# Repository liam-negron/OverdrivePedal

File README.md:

# OverdrivePedal
A custom overdrive guitar pedal with volume, drive, and tone control.\
Video demonstration: https://youtu.be/vQzezkZPXa8

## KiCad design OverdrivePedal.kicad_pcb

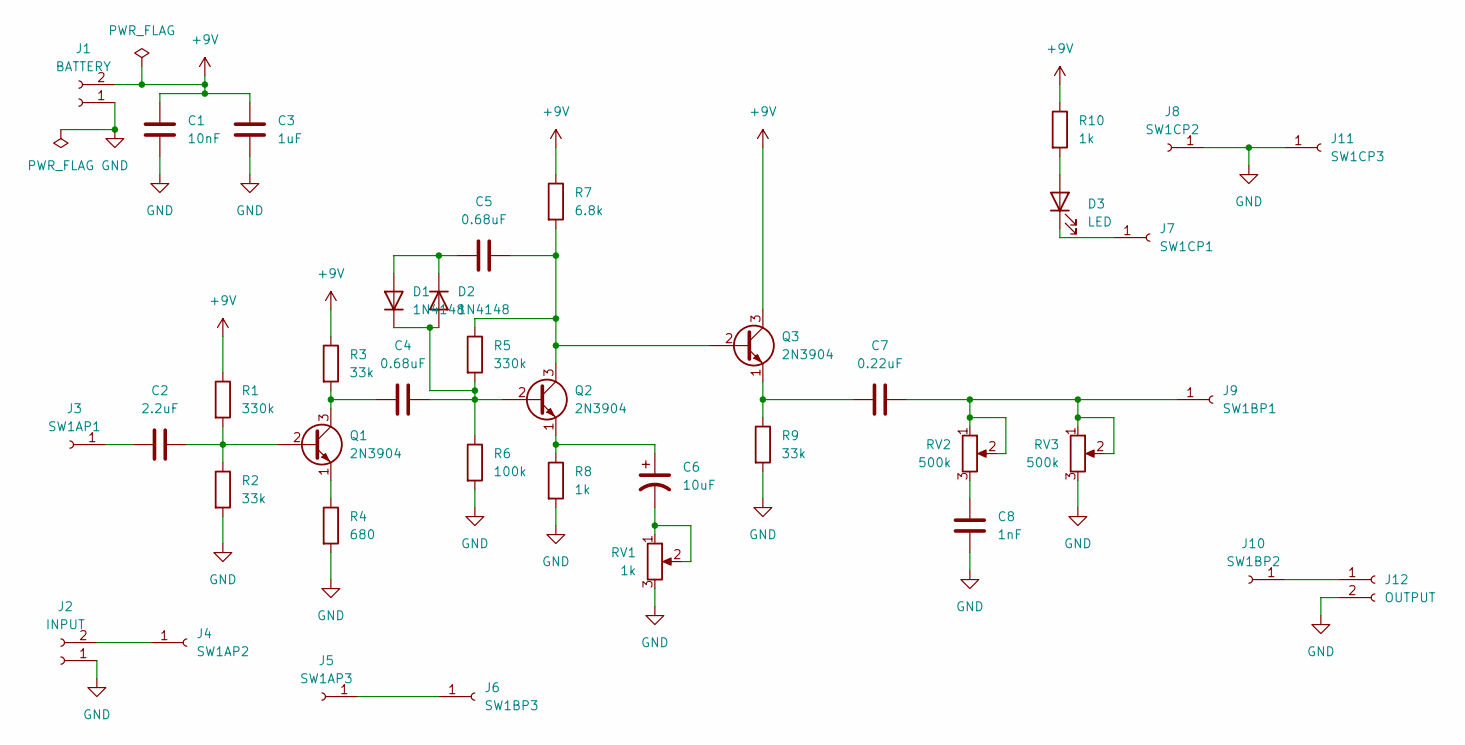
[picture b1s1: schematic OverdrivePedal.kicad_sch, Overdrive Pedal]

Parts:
C1: 10nF; C_Disc_D3.0mm_W1.6mm_P2.50mm
C2: 2.2uF; C_Disc_D3.0mm_W1.6mm_P2.50mm
C3: 1uF; C_Disc_D3.0mm_W1.6mm_P2.50mm
C4, C5: 0.68uF; C_Disc_D3.0mm_W1.6mm_P2.50mm
C6: 10uF; CP_Radial_D4.0mm_P2.00mm
C7: 0.22uF; C_Disc_D3.0mm_W1.6mm_P2.50mm
C8: 1nF; C_Disc_D3.0mm_W1.6mm_P2.50mm
D1, D2: 1N4148; D_DO-35_SOD27_P7.62mm_Horizontal
D3: LED; LED_D3.0mm
J1: BATTERY; PinSocket_1x02_P2.54mm_Vertical
J2: INPUT; PinSocket_1x02_P2.54mm_Vertical
J3: SW1AP1; Pin_D1.0mm_L10.0mm
J4: SW1AP2; Pin_D1.0mm_L10.0mm
J5: SW1AP3; Pin_D1.0mm_L10.0mm
J6: SW1BP3; Pin_D1.0mm_L10.0mm
J7: SW1CP1; Pin_D1.0mm_L10.0mm
J8: SW1CP2; Pin_D1.0mm_L10.0mm
J9: SW1BP1; Pin_D1.0mm_L10.0mm
J10: SW1BP2; Pin_D1.0mm_L10.0mm
J11: SW1CP3; Pin_D1.0mm_L10.0mm
J12: OUTPUT; PinSocket_1x02_P2.54mm_Vertical
Q1, Q2, Q3: 2N3904; TO-92_Inline
R1, R5: 330k; R_Axial_DIN0309_L9.0mm_D3.2mm_P12.70mm_Horizontal
R2, R3, R9: 33k; R_Axial_DIN0309_L9.0mm_D3.2mm_P12.70mm_Horizontal
R4: 680; R_Axial_DIN0309_L9.0mm_D3.2mm_P12.70mm_Horizontal
R6: 100k; R_Axial_DIN0309_L9.0mm_D3.2mm_P12.70mm_Horizontal
R7: 6.8k; R_Axial_DIN0309_L9.0mm_D3.2mm_P12.70mm_Horizontal
R8, R10: 1k; R_Axial_DIN0309_L9.0mm_D3.2mm_P12.70mm_Horizontal
RV1: 1k; Potentiometer_Bourns_3386C_Horizontal
RV2, RV3: 500k; Potentiometer_Bourns_3386C_Horizontal

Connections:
+9V: C1.1, C3.1, J1.2, Q3.3 (C), R1.1, R3.1, R7.1, R10.1
GND: C1.2, C3.2, C8.2, J1.1, J2.1, J8.1, J11.1, J12.2, R2.2, R4.2, R6.2, R8.2, R9.2, RV1.3, RV3.3
unnamed: C2.1, Q1.2 (B), R1.2, R2.1
unnamed: C2.2, J3.1
unnamed: C4.1, D1.1 (K), D2.2 (A), Q2.2 (B), R5.2, R6.1
unnamed: C4.2, Q1.3 (C), R3.2
unnamed: C5.1, Q2.3 (C), Q3.2 (B), R5.1, R7.2
unnamed: C5.2, D1.2 (A), D2.1 (K)
unnamed: C6.1, Q2.1 (E), R8.1
unnamed: C6.2, RV1.1, RV1.2
unnamed: C7.1, J9.1, RV2.1, RV2.2, RV3.1, RV3.2
unnamed: C7.2, Q3.1 (E), R9.1
unnamed: C8.1, RV2.3
unnamed: D3.1 (K), J7.1
unnamed: D3.2 (A), R10.2
unnamed: J2.2, J4.1
unnamed: J5.1, J6.1
unnamed: J10.1, J12.1
unnamed: Q1.1 (E), R4.1

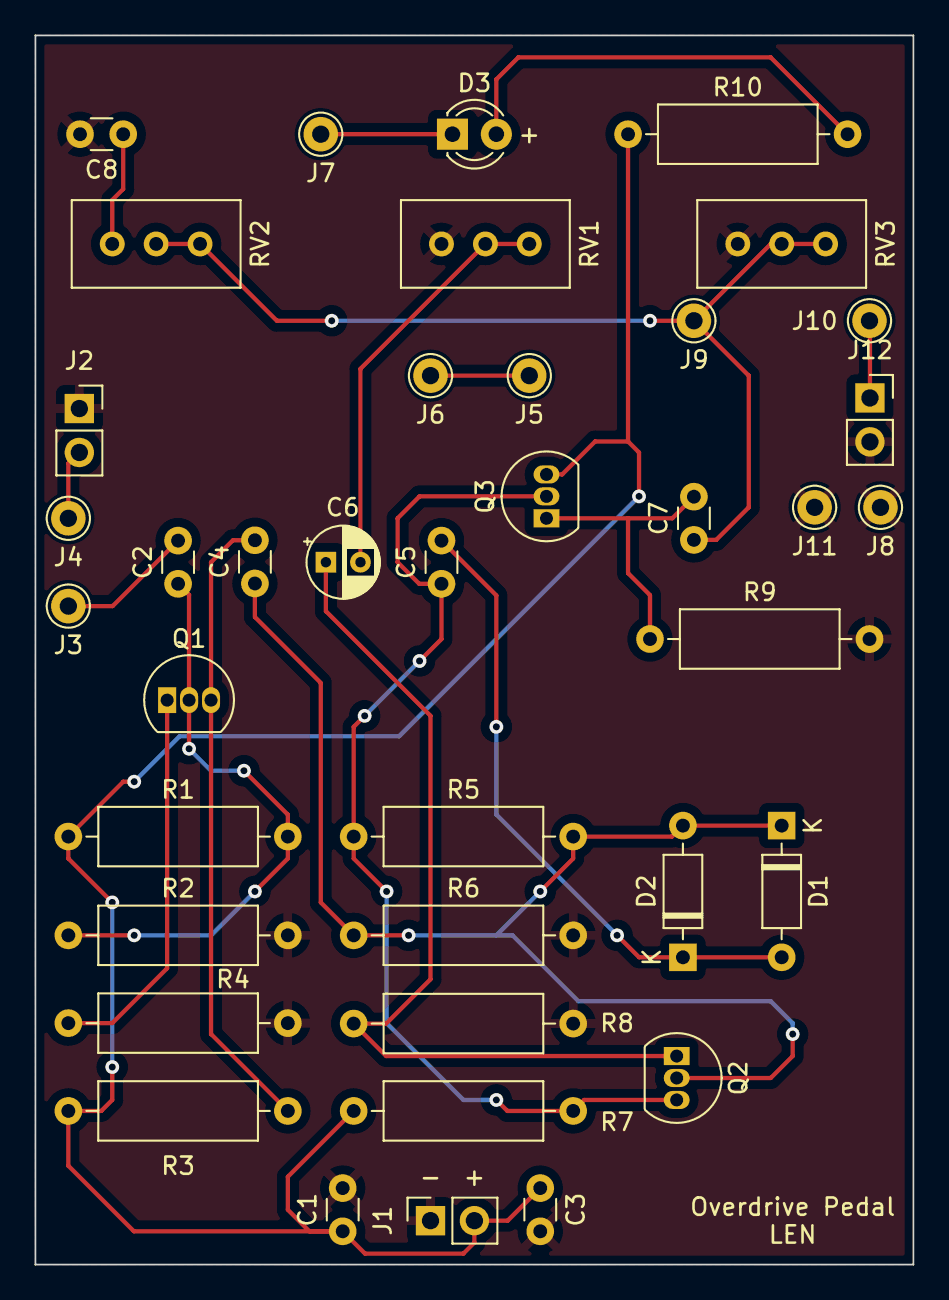
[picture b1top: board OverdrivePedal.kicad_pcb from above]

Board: 2 copper layers, 50.8 x 71.1 mm, 39 parts (0 on the bottom side), 19 nets.

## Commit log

2022-08-01 Added schematic files
2022-09-05 added kicad project files
2022-09-05 added schematic pdf
